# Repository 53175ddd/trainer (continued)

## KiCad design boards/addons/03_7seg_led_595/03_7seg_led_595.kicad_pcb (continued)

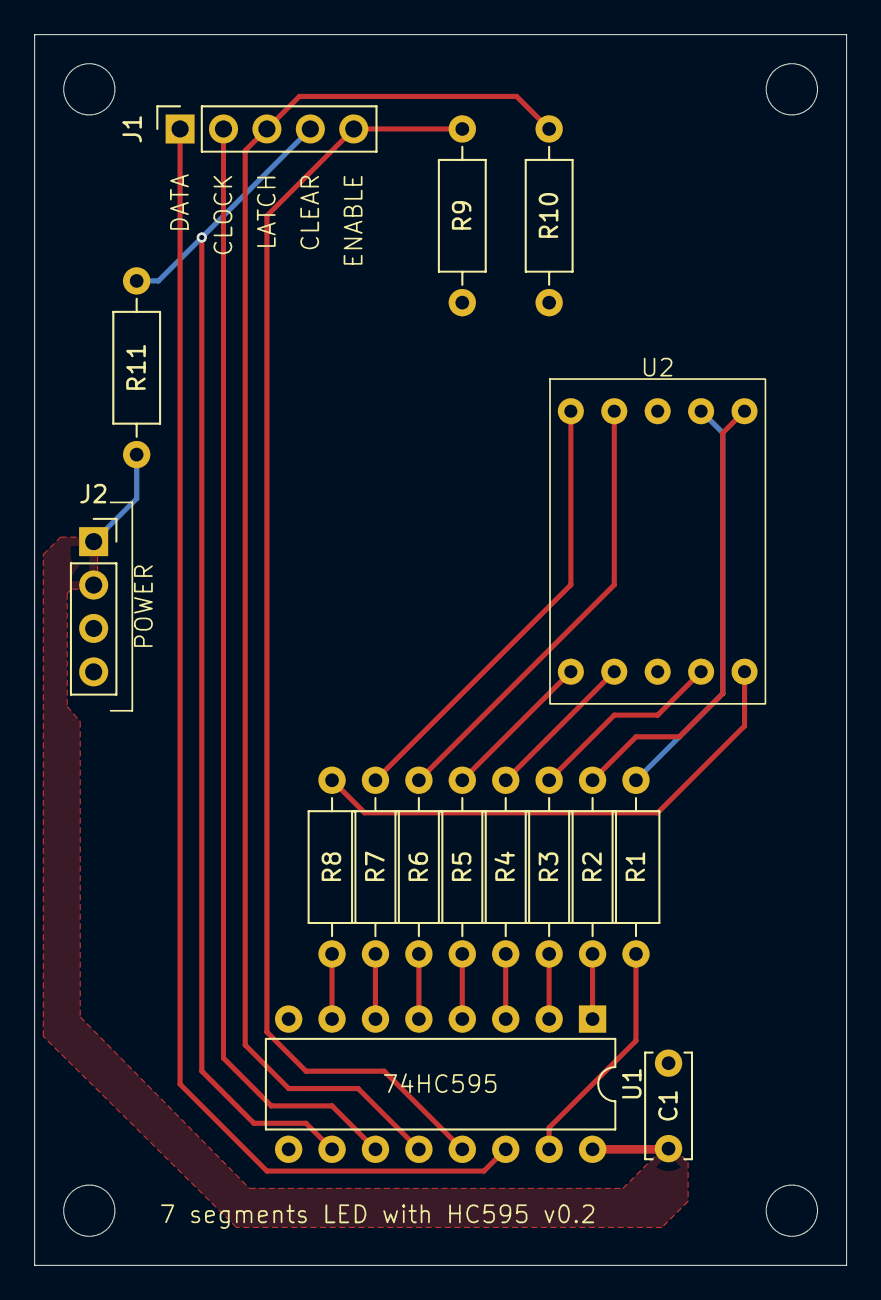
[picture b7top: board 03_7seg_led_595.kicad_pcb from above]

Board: 2 copper layers, 47.5 x 72.0 mm, 16 parts (0 on the bottom side), 23 nets.

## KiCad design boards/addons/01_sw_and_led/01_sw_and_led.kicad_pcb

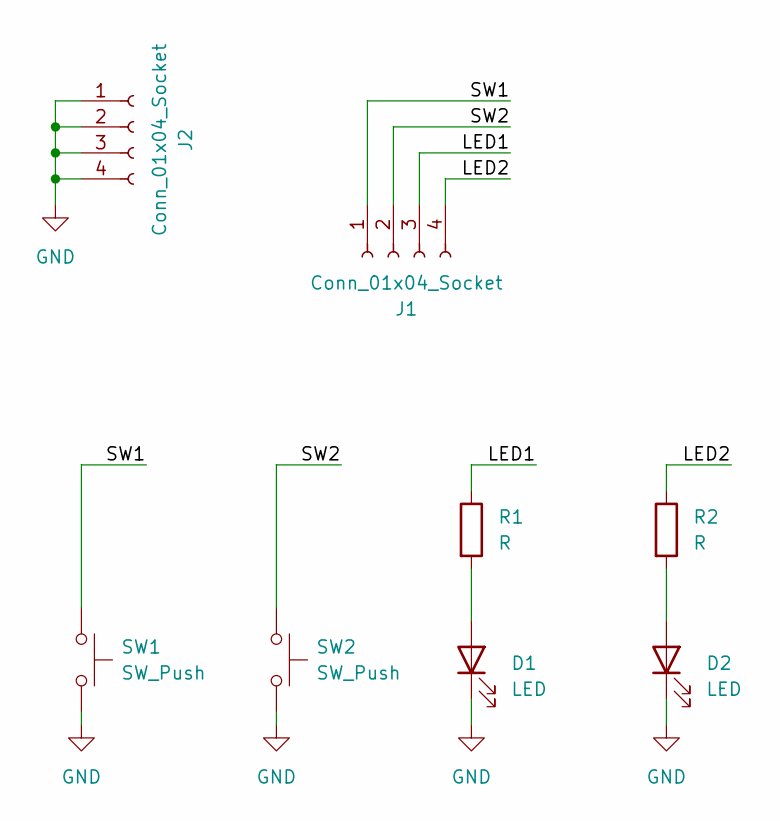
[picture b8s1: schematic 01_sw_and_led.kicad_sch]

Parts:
D1, D2: LED; LED_D5.0mm
J1, J2: Conn_01x04_Socket; PinSocket_1x04_P2.54mm_Vertical
R1, R2: R; R_Axial_DIN0207_L6.3mm_D2.5mm_P10.16mm_Horizontal
SW1, SW2: SW_Push; SW_PUSH-12mm

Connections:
/LED1: J1.3, R1.1
/LED2: J1.4, R2.1
/SW1: J1.1, SW1.1
/SW2: J1.2, SW2.1
GND: D1.1 (K), D2.1 (K), J2.1, J2.2, J2.3, J2.4, SW1.2, SW2.2
unnamed: D1.2 (A), R1.2
unnamed: D2.2 (A), R2.2

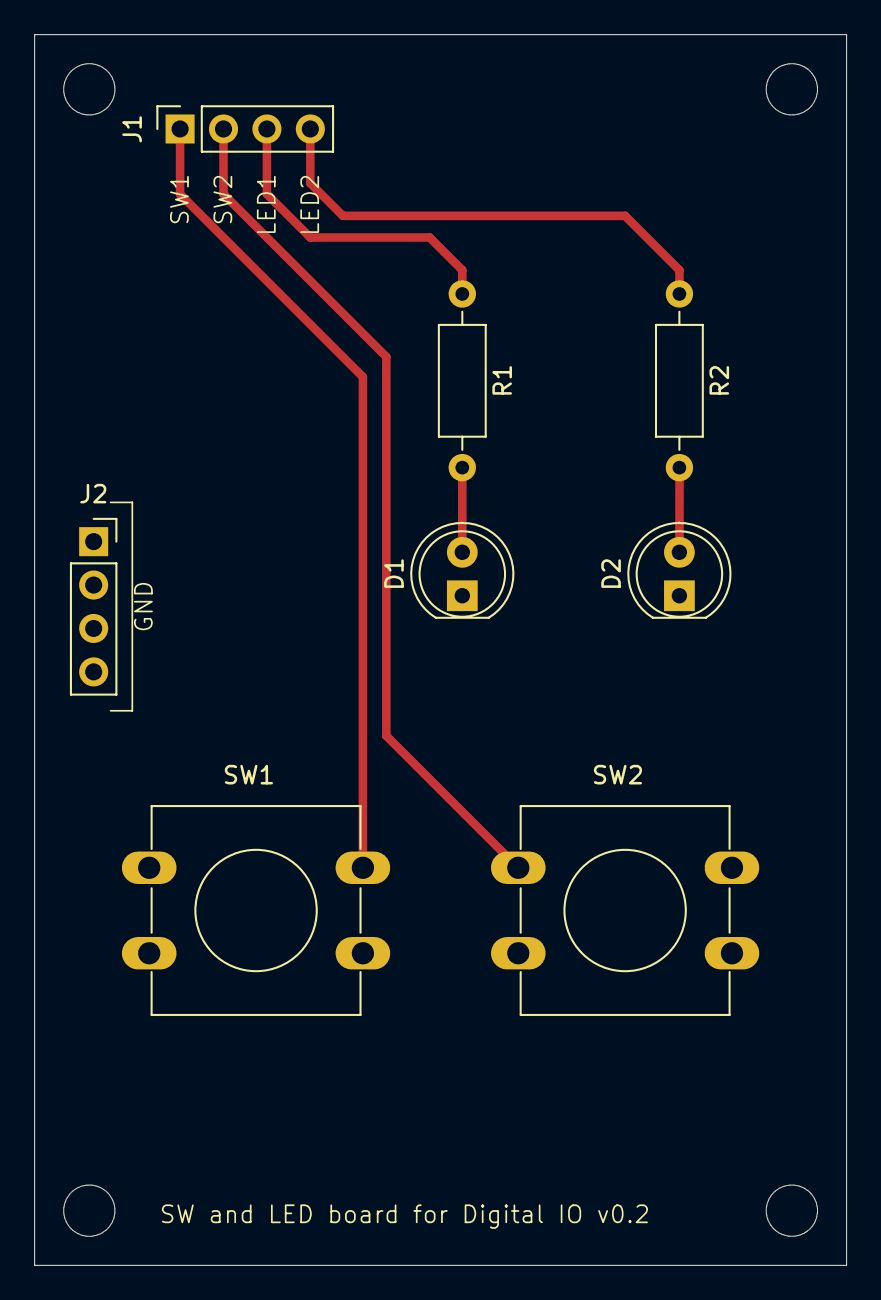
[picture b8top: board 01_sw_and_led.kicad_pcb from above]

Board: 2 copper layers, 47.5 x 72.0 mm, 8 parts (0 on the bottom side), 7 nets.

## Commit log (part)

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2026-01-02 create kicad project file
2026-01-02 create footprint and symbol of AE-RP2040
2026-01-10 暫定回路
2026-01-11 部品配置を概ね fix
2026-01-11 アノテーションの修正
2026-01-11 ベタを調整
2026-01-12 配線の取り回しを改善
2026-01-12 I2C の外部プルアップ用の回路を追加
2026-01-13 電源パターンを調整
2026-01-13 シルクの刻印をいい感じにした
2026-01-13 Pico の両側にピンソケット・ピンヘッダを追加
2026-01-14 Pico の両側に IO 番号の刻印を追加
2026-01-14 配線を微修正
2026-01-14 外部電源追加
2026-01-14 trainer-nano を削除
    trainer-nano 作るのやめて pico 一本で進めることにした
2026-01-14 PCBA 用のパーツ番号を追加
2026-01-14 partslist.md
2026-01-14 配線を修正
2026-01-14 シルクの刻印を追加
2026-01-15 電源プレーンの修正と via 打ち職人
2026-01-15 ズレてたシルクを戻した
2026-01-15 additional via 打ち職人
2026-01-15 シルクのバージョンを改番
2026-01-17 ベタが気に食わなかったので修正
2026-01-18 L チカ基板の pj 作成
2026-01-18 回路図書いて FP 割り当て
2026-01-18 大雑把に部品配置
2026-01-18 電源と入出力のピンソケット追加
2026-01-18 ピンソケット配置
2026-01-18 配置調整
2026-01-18 AW 引いた
2026-01-18 7 セグの pj
2026-01-18 駆動回路だけ書いた
2026-01-19 パターンが微妙にズレてたので直した
2026-01-19 ピンヘッダをピンソケットに変更
2026-02-15 もはや間違い探しレベルの微修正
2026-02-15 スイッチのプルアップ抵抗はなくしました
2026-02-15 LED のシンボルとフットプリント
2026-02-15 かいろず
2026-02-15 7seg その 1
2026-02-16 電源ベタの修正
2026-02-16 電源のシルク追加
2026-02-16 ゴミが残ってたので削除
2026-02-16 via の打ち直し
2026-02-16 電源ベタ修正
2026-02-16 シルク追加
2026-02-16 バージョンアップ
2026-02-16 ガーバー出力
2026-02-16 またもベタを微修正
2026-02-22 ベタの修正と via の打ち直し
2026-02-22 kicad pj
2026-02-22 fp / sym 登録
2026-02-28 ベタの微修正
2026-02-28 配線テコ入れ
2026-03-02 修正は続くよどこまでも
2026-03-02 AW こねこね
2026-03-02 ナンバリング修正
2026-03-02 シルクの追加とベタのテコ入れ
2026-03-02 シルクの追加とベタのテコ入れ その 2
2026-03-02 配置の修正とピンアサインの刻印の追加
2026-03-02 製造ファイル出力
2026-04-02 Add board image link for trainer-pico
    Added a link to the board image for the trainer-pico.
2026-04-05 サブ基板の固定方法を変更
2026-04-05 ベタ形状変更
